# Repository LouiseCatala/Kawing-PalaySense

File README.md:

<div align="center">

# KAWING PalaySense

### The IoT-Based Grain Moisture Assessment Device of KAWING

An ESP32-based IoT device designed to assess rice grain moisture and transmit readings to the KAWING Web-Based Smart Post-Harvest Coordination Platform.

*Figure 1. KAWING PalaySense IoT Hardware Wiring Diagram*

</div>

---

## Overview

**KAWING PalaySense** is the IoT hardware component of **KAWING (Knowledge-based Agricultural Workflow Integration Network Gateway)**, a web-based smart post-harvest coordination platform for rice farmers in Magalang, Pampanga.

The device uses an **ESP32** and **HW-390 capacitive moisture sensor** to estimate grain moisture content, classify the reading, and send the results to the KAWING website through Wi-Fi.

## Key Features

- Grain moisture assessment
- Automatic moisture classification
- ESP32-based sensor processing
- Wi-Fi and REST API integration
- Data transmission to the KAWING web platform
- Rechargeable battery-powered operation

## Hardware Components

| Component | Purpose |
|---|---|
| ESP32 DevKit V1 | Main microcontroller |
| HW-390 V2.0.0 | Capacitive moisture sensor |
| TP4056 | Battery charging module |
| MT3608 | DC-DC boost converter |
| 3.7V Li-ion Battery | Power supply |
| ON/OFF Switch | Power control |

## Pin Connections

| HW-390 Sensor | ESP32 |
|---|---|
| VCC | 3V3 |
| AOUT | GPIO34 |
| GND | GND |

**Power Connection:**

Battery → TP4056 → ON/OFF Switch → MT3608 (5V) → ESP32

The MT3608 output must be verified at 5V before connecting to the ESP32.

## Moisture Classification

| Moisture Content | Classification |
|---|---|
| Above 17% | Wet |
| 15% – 17% | Moderate |
| Above 11% to below 15% | Dry |
| 11% and below | Risk of Grain Breakage |

These classifications use estimated moisture values and require calibration against a reference grain moisture meter.

## How It Works

1. The HW-390 sensor detects changes in capacitance.
2. The ESP32 reads the sensor through GPIO34.
3. The firmware calculates an estimated moisture percentage.
4. The reading is classified based on its moisture level.
5. The ESP32 sends the results to the KAWING REST API through Wi-Fi.
6. The KAWING website receives and manages the moisture assessment data.

## Getting Started

1. Connect the hardware according to the wiring diagram.
2. Open the PalaySense `.ino` file in Arduino IDE.
3. Configure your Wi-Fi credentials and KAWING API settings privately.
4. Select the ESP32 board and correct COM port.
5. Upload the firmware.
6. Open Serial Monitor at **115200 baud** to view sensor readings.

> **Note:** PalaySense is an academic prototype. Moisture readings require calibration and validation before practical agricultural use.

---

<div align="center">

### KAWING PalaySense

**IoT-Integrated Grain Moisture Assessment for Smart Post-Harvest Management**

Part of the KAWING Research Project

</div>

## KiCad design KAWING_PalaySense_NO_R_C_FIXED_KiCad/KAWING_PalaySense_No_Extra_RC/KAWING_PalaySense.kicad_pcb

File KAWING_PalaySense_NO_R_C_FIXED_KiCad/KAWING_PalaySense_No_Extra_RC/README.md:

# KAWING PalaySense — Actual module-based circuit, WITHOUT added external R/C

This is the corrected KiCad project derived from your existing on-board power carrier.

## Actual board components only
- **U1:** ESP32 DevKit V1 30-pin (3.3 V logic)
- **J2:** TP4056 1-cell protected charging *module*, board-mounted
- **J3:** MT3608 adjustable boost converter *module*, board-mounted
- **SW1:** Two-terminal latching ON/OFF switch, board-mounted
- **J1:** 2-pin connector to external 3.7 V Li-ion battery
- **J4:** 3-pin connector to external HW-390 V2.0.0 sensor

**Removed:** R1 (1 kΩ), C1 (100 nF), C2 (100 µF), C3 (100 nF). No extra standalone resistors or capacitors appear in the schematic, PCB, or component models. Existing components *inside* TP4056, MT3608, and ESP32 modules are still depicted as part of those prefabricated modules, as they should be.

## Wiring matching your Arduino program
- HW-390 **AOUT → ESP32 GPIO34** directly, with no series resistor or separate ADC filter capacitor.
- HW-390 **VCC → ESP32 3V3**, **GND → system GND**.
- Battery positive/negative → protected TP4056 **B+/B−**.
- TP4056 **OUT+ → SW1 → MT3608 IN+**.
- TP4056 **OUT− → MT3608 IN−**, system GND. **Do not bridge TP4056 B− and OUT−.**
- MT3608 boosted **5.0V → ESP32 VIN/5V**, output GND → system GND.
- Wi-Fi/Internet: ESP32 radio, not a cable connector.

## How to open
1. Extract the ZIP fully, preserving `KAWING.3dshapes` and `KAWING.pretty`.
2. Open `KAWING_PalaySense.kicad_pro` in KiCad.
3. Open `.kicad_pcb`, and select **View → 3D Viewer** (Alt+3).
4. Keep component models enabled under 3D Viewer display options.

## Fabrication limitations
PCB module footprints are approximations of your TP4056, MT3608, switch and DevKit, **not dimension-verified direct-solder patterns**. Measure actual boards, headers, switch pins and USB positions before physical manufacturing. TP4056 and MT3608 are mounted to the carrier with insulation and wired to identified pads if the breakout hole positions do not match. Do not treat this as a plug-in footprint without verification.

**This revision is a prototype electrical wiring layout, NOT fabrication-certified**. KiCad CLI/GUI ERC/DRC and physical verification must be completed on the exact hardware, especially copper clearances/shorts and the ESP32 antenna keepout. Do not connect ESP32 external 5V and USB power simultaneously without confirming the specific DevKit protection. Adjust MT3608 to 5.0V before connecting ESP32.

## Routing revision
Prior 5V trace intersected the direct ADC signal on the same layer. This package moves the 5V feed onto the rear copper layer through one via and routes it to the ESP32 VIN pad. The replaced filter-capacitor ground inter-layer transitions are now actual vias. Geometric checks of all routed track pairs and through-hole pads detected zero cross-net copper intersections; this is NOT a replacement for a KiCad DRC.

## Updated deliverables
- `PCB_Clean_Top_Layout.png` clean 2D board layout
- `Wiring_Overview.png` connection overview
- `3D_Assembly/KAWING_No_Extra_RC_Isometric.png` cleaned 3D render
- `3D_Assembly/KAWING_No_Extra_RC_Top.png` cleaned 3D top render
- `KAWING_PalaySense_No_Extra_RC.step` approximate mechanical STEP CAD
- `3D_Assembly/KAWING_PalaySense_No_Extra_RC.glb` 3D assembly
- `KAWING_PalaySense_STEP_Alternative.kicad_pcb` alternate VRML model references to STEP for KiCad 3D Viewer

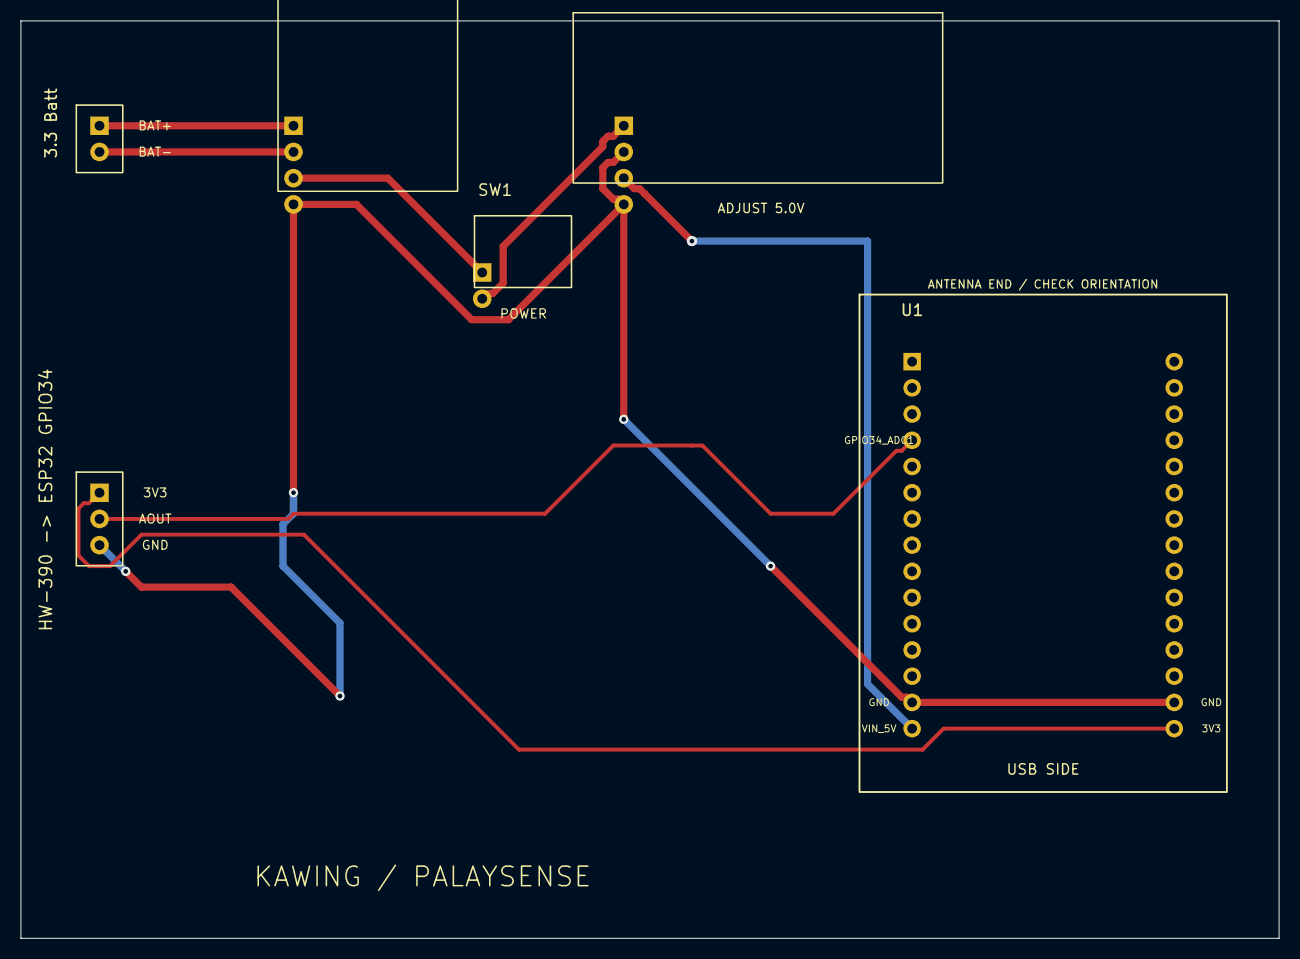
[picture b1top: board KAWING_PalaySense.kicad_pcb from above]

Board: 2 copper layers, 121.9 x 88.9 mm, 6 parts (0 on the bottom side), 8 nets.

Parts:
3.3 Batt: 3.7V 1S BATTERY; Wire_Header_1x2_P2.54mm
J2: TP4056 protected 1S charger / ON-BOARD; TP4056_Protected_Module_Onboard
J3: MT3608 boost module / ON-BOARD; MT3608_Boost_Module_Onboard
J4: HW-390 V2.0.0; Wire_Header_1x3_P2.54mm
SW1: SPST ON/OFF / ON-BOARD; SPST_Slide_Power_Switch_Onboard
U1: ESP32 DevKit V1 30-pin; ESP32_DevKitV1_30PIN_25.4mm

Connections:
BATTERY_MINUS: 3.3 Batt.2, J2.2
BATTERY_PLUS: 3.3 Batt.1, J2.1
BOOST_INPUT_PLUS: J3.1, SW1.2
PLUS_5V: J3.3, U1.15
PROTECTED_PLUS: J2.3, SW1.1
SENSOR_3V3: J4.1, U1.30
SENSOR_AOUT: J4.2, U1.4
SYSTEM_GND: J2.4, J3.2, J3.4, J4.3, U1.14, U1.29
